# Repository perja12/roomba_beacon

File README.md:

# IR Beacon for Roomba

Quick links: [Schematic](https://perja12.github.io/roomba_beacon/kicad/ir_beacon/ir_beacon.pdf) | [Interactive BOM](https://perja12.github.io/roomba_beacon/kicad/ir_beacon/bom/ibom.html)

This project describes an IR beacon that can be used with certain Roomba vacuum cleaners. The beacon can be used to prevent the vacuum cleaner from entering a room or other off-limit zones. The vacuum cleaner will simply turn around when it receives the infrared light emitted from the beacon.

The project is inspired by a similar project from http://gregthielen.me/blogstuff/2017/06/27/roomba-virtual-wall/ and the timings for IR LED is taken directly from that page.

## Design

The circuit itself is simple enough; when the push button is pressed, the IR LED will flash in a given pattern. To save battery the duration is limited to one hour (configurable). In addition there is a green indicator LED that will flash once when the device is turned on and twice when turned off.

An ATtiny85V is used without any voltage regulator as it can operate with a voltage from 1.8 to 5.5V. The device is powered by two AAA alkaline batteries and the battery holder is soldered to the PCB. As the ATtiny85 have maximum current of 40 mA per pin and the IR LED (Vishay TSAL4000) has a forward current of 100 mA, we will need a transistor (MMBT3904) to switch the IR LED.

# Power consumption

There are two modes of operation:

1) Sleep mode: the IR LED is off and the MCU is in deep sleep. The current consumption is a couple of uA.

2) The average current consumption during active mode (when blinking the IR LED) is about 3.3 mA and can be lowered by using SLEEP_IDLE to save power and wake up when 132 ms have passed.

# Push button on/off switch

The circuit uses a power latch implemented by using special instructions that skips resetting a particular variable to zero during reset (see the _power_ variable in the code).  The push button is connected to the RESET pin and when pressed it will reset the MCU. The setup function toggles the _power_ variable and the circuit either goes to sleep or starts blinking the LED. With such a design it is important to have low sleep current. The solution is described here: http://www.technoblogy.com/show?VOO.

# Configurable on-duration

Depending on the route the vacuum cleaner chooses one can decide how many hours the device will be on. The user can configure this by setting two DIP switches. The duration is measured by using the number of milliseconds since the device was reset. The accuracy of this timer is not very good and can be off by several minutes. But for this purpose it works well enough.

# Detect low battery (not implemented)

On start up the indicator LED will blink rapidly if it is time to replace the batteries (around 2V). This is implemented by setting the internal reference voltage as ADC input and the target VCC as the ADC reference. The solution is described in this application note from Microchip: http://ww1.microchip.com/downloads/en/Appnotes/00002447A.pdf

# How to build

Install the ATTinyCore and use the following settings in the Arduino IDE

* Uses ATTinyCore: https://github.com/SpenceKonde/ATTinyCore
* 8 MHz internal clock
* B.O.D. disabled to save power

There is also a Makefile that uses [arduino-cli](https://www.arduino.cc/pro/cli).

# Enclosure

The PCB is designed so that it fits the Hammond 1591 ABS multipurpose enclosure and can be mounted directly without any standoffs. Only three additional holes are needed. Using one of the transparent boxes makes it easy to see where to drill. Note that there is a slight angle on the sides so the box wont stand exactly at 90 degrees, but close enough.

# Improvements

List of improvements that can be done:

* Clean up the layout and make it more compact.
* Replace delay in code with timers.
* Blink the LED now and then to show that it is on.

# Images

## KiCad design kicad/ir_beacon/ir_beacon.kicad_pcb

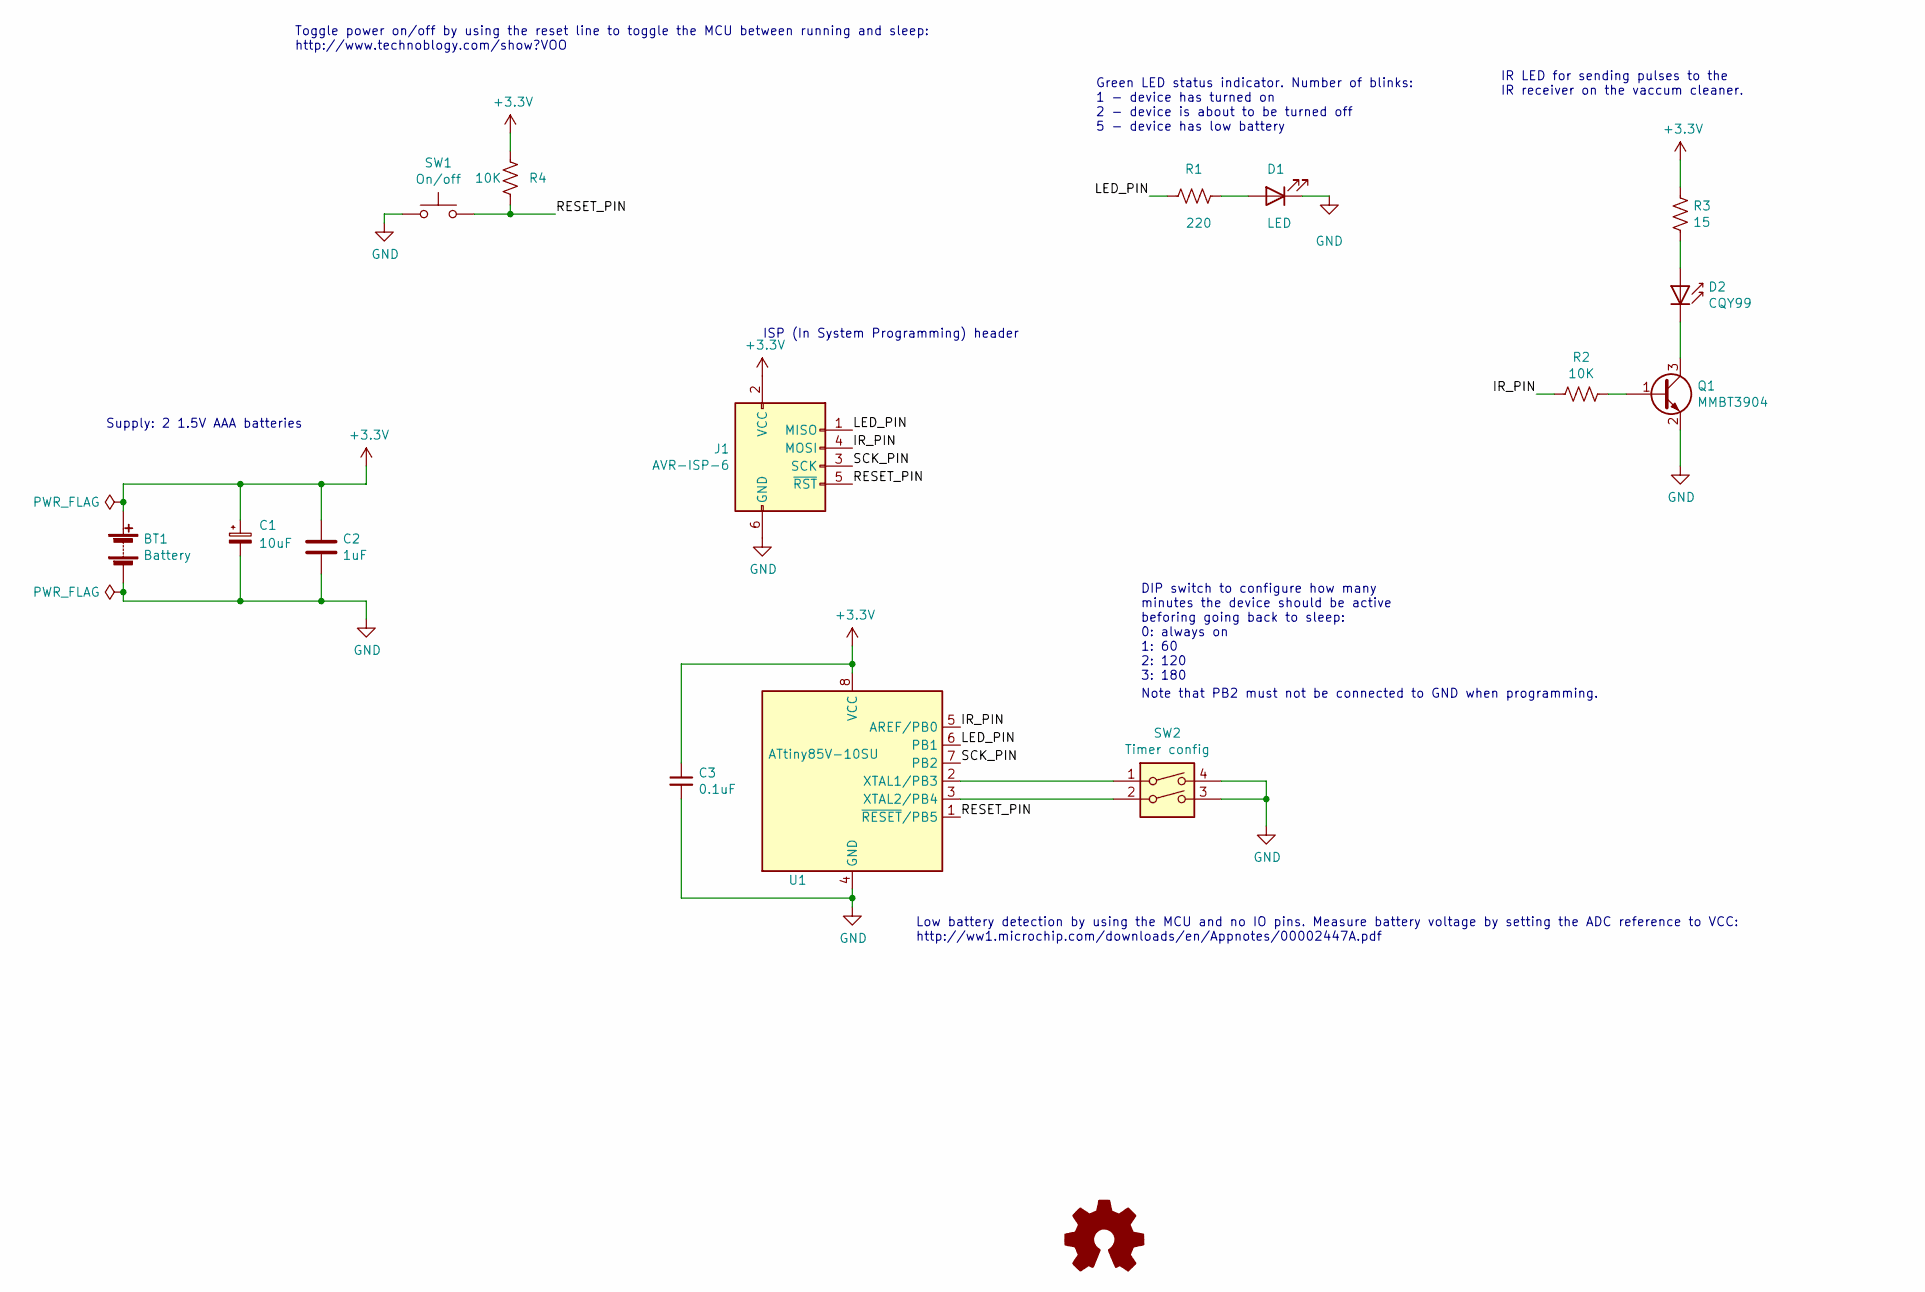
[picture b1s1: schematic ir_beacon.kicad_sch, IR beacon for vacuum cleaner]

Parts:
BT1: Battery; BatteryHolder_Keystone_2468_2xAAA
C1: 10uF; CP_EIA-6032-28_Kemet-C_Pad2.25x2.35mm_HandSolder
C2: 1uF; C_0805_2012Metric
C3: 0.1uF; C_0805_2012Metric
D1: LED; LED_D5.0mm
D2: CQY99; LED_D5.0mm_IRGrey
J1: AVR-ISP-6; IDC-Header_2x03_P2.54mm_Vertical
Q1: MMBT3904; SOT-23
R1: 220; R_0805_2012Metric
R2, R4: 10K; R_0805_2012Metric
R3: 15; R_0805_2012Metric
SW1: On/off; SW_PUSH_6mm
SW2: Timer config; SW_DIP_SPSTx02_Slide_9.78x7.26mm_W7.62mm_P2.54mm
U1: ATtiny85V-10SU; SOIJ-8_5.3x5.3mm_P1.27mm

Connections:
+3V3: BT1.1 (+), C1.1, C2.1, C3.1, J1.2 (VCC), R3.1, R4.1, U1.8 (VCC)
/IR_PIN: J1.4 (MOSI), R2.1, U1.5 (AREF/PB0)
/LED_PIN: J1.1 (MISO), R1.1, U1.6 (PB1)
/RESET_PIN: J1.5 (~RST), R4.2, SW1.2, U1.1 (~RESET/PB5)
/SCK_PIN: J1.3 (SCK), U1.7 (PB2)
GND: BT1.2 (-), C1.2, C2.2, C3.2, D1.1 (K), J1.6 (GND), Q1.2 (E), SW1.1, SW2.3, SW2.4, U1.4 (GND)
unnamed: D1.2 (A), R1.2
unnamed: D2.1 (K), Q1.3 (C)
unnamed: D2.2 (A), R3.2
unnamed: Q1.1 (B), R2.2
unnamed: SW2.1, U1.2 (XTAL1/PB3)
unnamed: SW2.2, U1.3 (XTAL2/PB4)

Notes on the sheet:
ISP (In System Programming) header
Low battery detection by using the MCU and no IO pins. Measure battery voltage by setting the ADC reference to VCC: http://ww1.microchip.com/downloads/en/Appnotes/00002447A.pdf
Note that PB2 must not be connected to GND when programming.
Toggle power on/off by using the reset line to toggle the MCU between running and sleep: http://www.technoblogy.com/show?VOO
DIP switch to configure how many minutes the device should be active beforing going back to sleep: 0: always on 1: 60 2: 120 3: 180
Green LED status indicator. Number of blinks: 1 - device has turned on 2 - device is about to be turned off 5 - device has low battery
Supply: 2 1.5V AAA batteries
IR LED for sending pulses to the IR receiver on the vaccum cleaner.

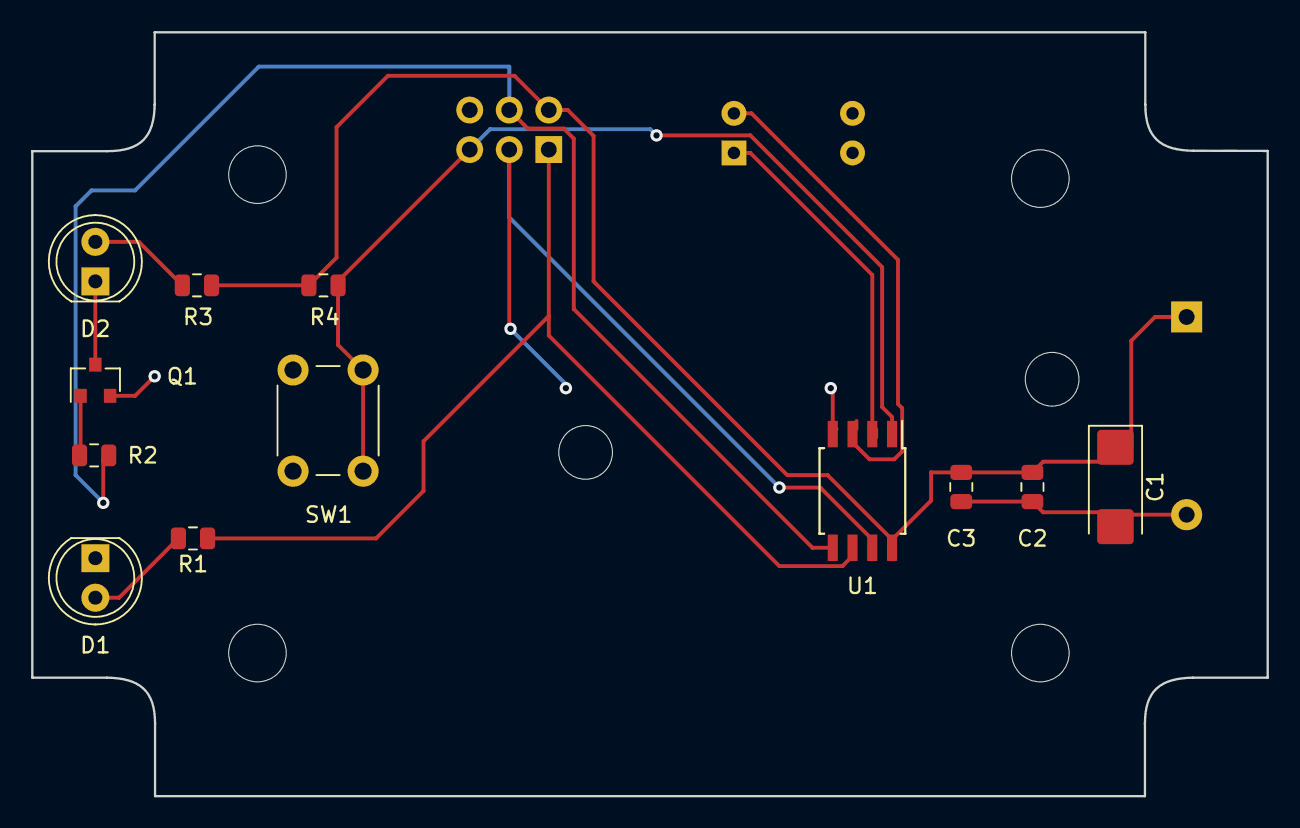
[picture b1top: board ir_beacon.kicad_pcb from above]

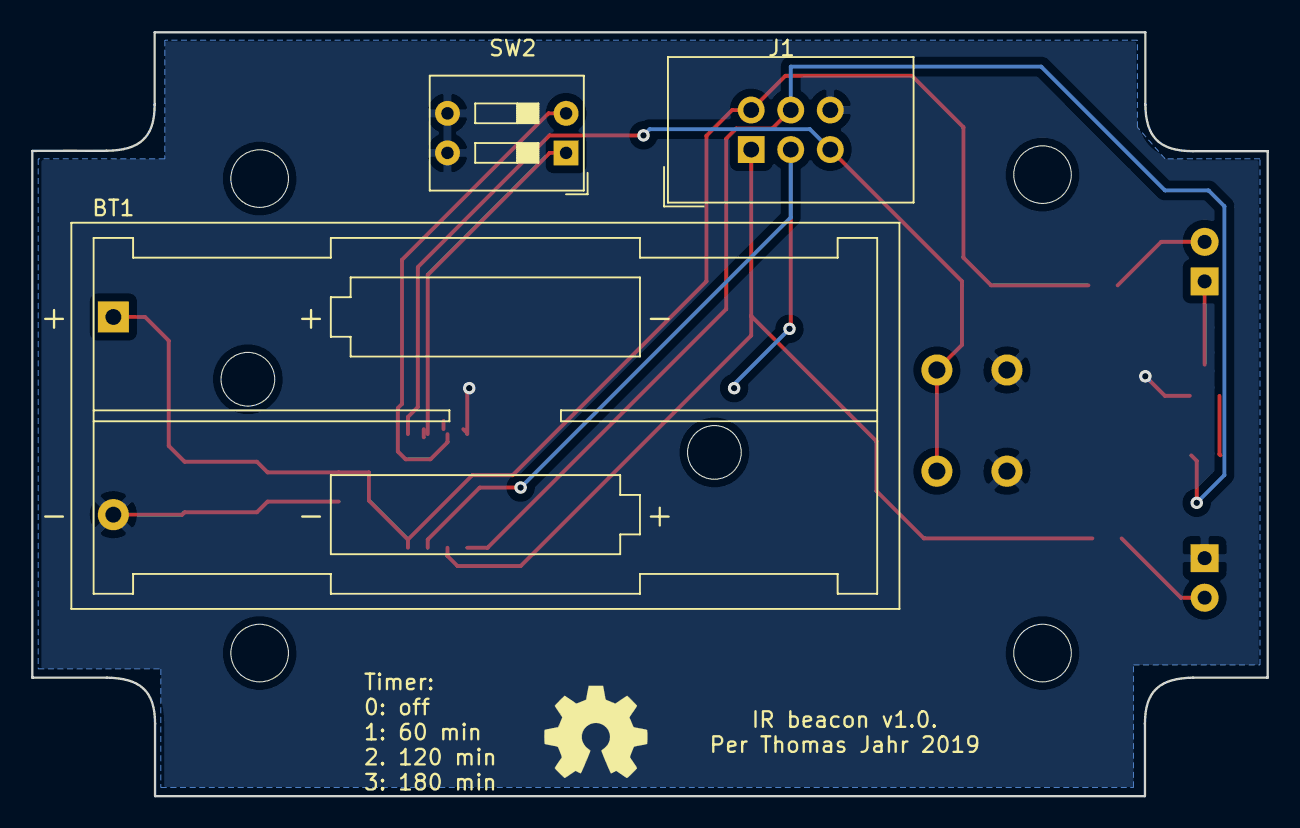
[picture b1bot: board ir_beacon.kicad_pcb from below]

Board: 2 copper layers, 79.4 x 49.1 mm, 15 parts (3 on the bottom side), 12 nets.

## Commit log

2019-12-05 Initial commit.
2019-12-16 Initial commit of Arduino sketch for beacon. Uses 3.3 mA in active mode.
2020-01-22 Rename files and update README.
2022-04-23 Cleanup a bit, add images and convert to KiCAD 6.
2022-04-23 Add PDF of schematic.
2022-04-23 Add ibom html.
2022-04-23 Add links to README.
2022-04-23 Add Makefile and update README again.
